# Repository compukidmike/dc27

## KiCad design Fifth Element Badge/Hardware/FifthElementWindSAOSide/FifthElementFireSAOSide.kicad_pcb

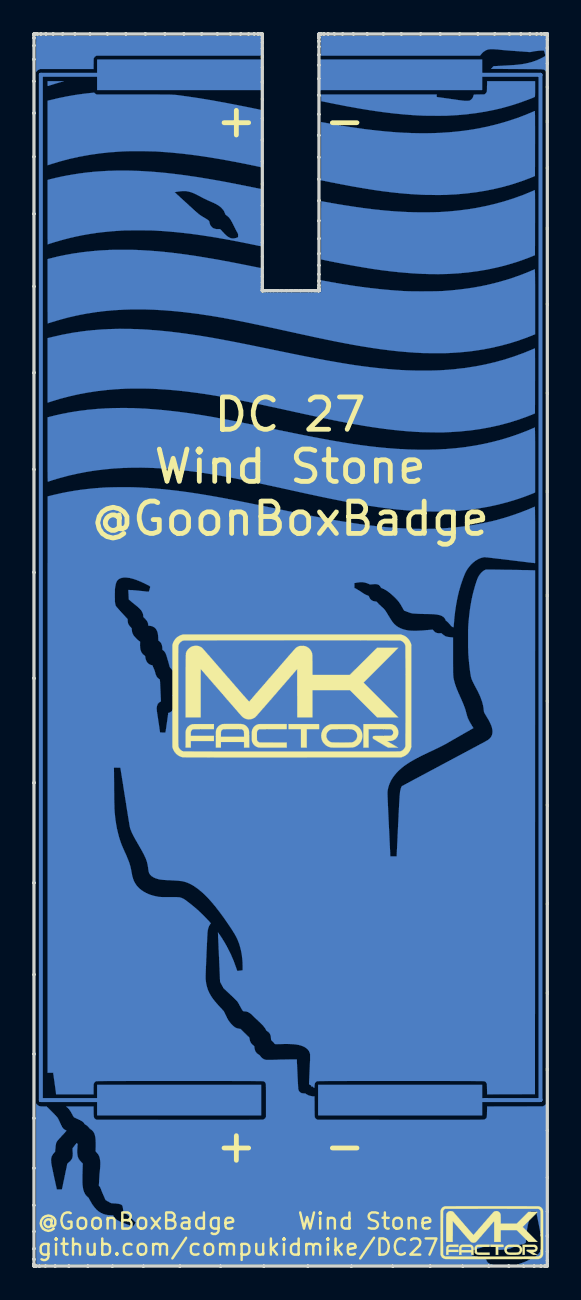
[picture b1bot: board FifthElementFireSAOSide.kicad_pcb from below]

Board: 2 copper layers, 31.8 x 76.2 mm, 3 parts (2 on the bottom side), 2 nets.

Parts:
BT1, BT2: Battery_Cell; FifthElementB2BConnector
Ref**: Val**; WindSide

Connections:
unnamed: BT1.2, BT2.2
unnamed: BT1.1, BT2.1
